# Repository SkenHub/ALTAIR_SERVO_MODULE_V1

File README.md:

# ALTAIR_SERVO_MODULE_V1
ALTAIR_SERVO_MODULE_V1 サーボモータ×５のモジュール　stm32f4446
作者の↓
https://github.com/Altairu/ALTAIR_SERVO_MODULE_V1.git

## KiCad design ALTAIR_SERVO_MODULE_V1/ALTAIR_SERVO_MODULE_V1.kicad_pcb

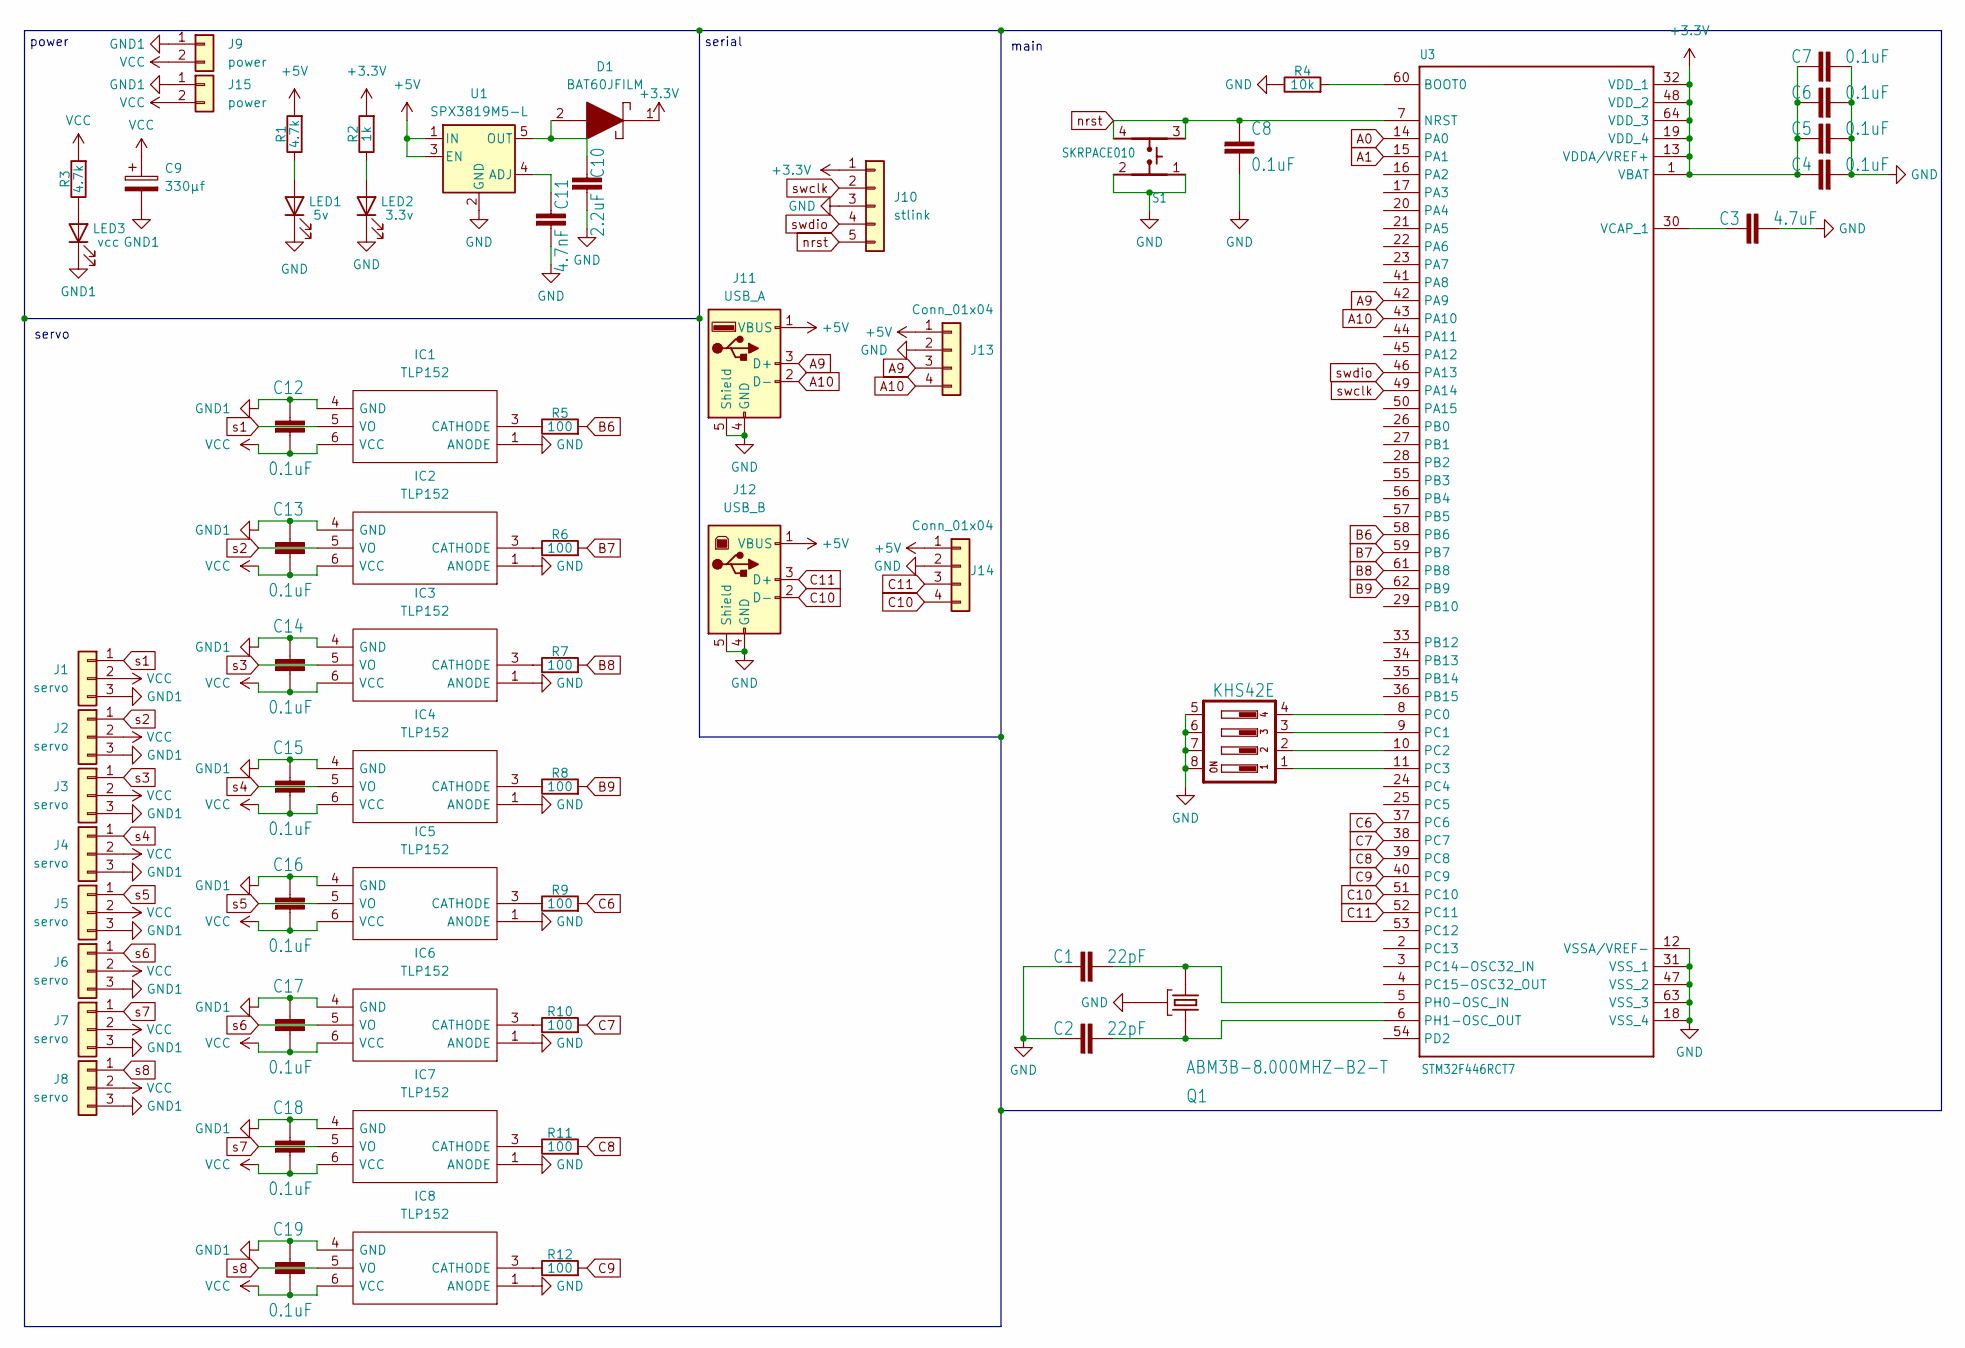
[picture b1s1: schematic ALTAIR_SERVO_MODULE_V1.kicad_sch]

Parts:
C1, C2: 22pF; C_0603_1608Metric
C3: 4.7uF; C_0603_1608Metric
C4, C5, C6, C7, C8, C12, C13, C14, C15, C16, C17, C18, C19: 0.1uF; C_0603_1608Metric
C9: 330μf; CP_Elec_10x10
C10: 2.2uF; C_0603_1608Metric
C11: 4.7nF; C_0603_1608Metric
D1: BAT60JFILM; SOD2513X117N; Manufacturer_Part_Number BAT60JFILM; Mouser Part Number 511-BAT60JFILM
IC1, IC2, IC3, IC4, IC5, IC6, IC7, IC8: TLP152; 11-4L1S_5-PIN-SOIC_; Manufacturer_Part_Number TLP152; Mouser Part Number N/A
J1, J2, J3, J4, J5, J6, J7, J8: servo; JST_XA_S03B-XASK-1_1x03_P2.50mm_Horizontal
J9, J15: power; AMASS_XT60PW-M_1x02_P7.20mm_Horizontal
J10: stlink; JST_XA_S05B-XASK-1_1x05_P2.50mm_Horizontal
J11: USB_A; USB_A_Molex_67643_Horizontal
J12: USB_B; USB_B_Lumberg_2411_02_Horizontal
J13, J14: Conn_01x04; JST_XA_B04B-XASK-1_1x04_P2.50mm_Vertical
LED1: 5v; LED_0603_1608Metric
LED2: 3.3v; LED_0603_1608Metric
LED3: vcc; LED_0603_1608Metric
Q1: ABM3B-8.000MHZ-B2-T; Crystal_SMD_Abracon_ABM3B-4Pin_5.0x3.2mm
R1, R3: 4.7k; R_0603_1608Metric
R2: 1k; R_0603_1608Metric
R4: 10k; R_0603_1608Metric
R5, R6, R7, R8, R9, R10, R11, R12: 100; R_0603_1608Metric
S1: SKRPACE010; SMT_4.2X3.2_
S2: KHS42E; SOIC127P600X175-8N
U1: SPX3819M5-L; SOT-23-5
U3: STM32F446RCT7; QFP50P1200X1200X160-64N

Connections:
+3.3V: C4.1, C5.1, C6.1, C7.1, D1.1, J10.1, R2.2, U3.1 (VBAT), U3.13 (VDDA/VREF+), U3.19 (VDD_4), U3.32 (VDD_1), U3.48 (VDD_2), U3.64 (VDD_3)
+5V: J11.1 (VBUS), J12.1 (VBUS), J13.1, J14.1, R1.2, U1.1 (IN), U1.3 (EN)
A0: U3.14 (PA0)
A1: U3.15 (PA1)
A9: J11.3 (D+), J13.3, U3.42 (PA9)
A10: J11.2 (D-), J13.4, U3.43 (PA10)
B6: R5.2, U3.58 (PB6)
B7: R6.2, U3.59 (PB7)
B8: R7.2, U3.61 (PB8)
B9: R8.2, U3.62 (PB9)
C6: R9.2, U3.37 (PC6)
C7: R10.2, U3.38 (PC7)
C8: R11.2, U3.39 (PC8)
C9: R12.2, U3.40 (PC9)
C10: J12.2 (D-), J14.4, U3.51 (PC10)
C11: J12.3 (D+), J14.3, U3.52 (PC11)
GND: C1.1, C2.1, C3.2, C4.2, C5.2, C6.2, C7.2, C8.2, C10.2, C11.2, IC1.1 (ANODE), IC2.1 (ANODE), IC3.1 (ANODE), IC4.1 (ANODE), IC5.1 (ANODE), IC6.1 (ANODE), IC7.1 (ANODE), IC8.1 (ANODE), J10.3, J11.4 (GND), J11.5 (Shield), J12.4 (GND), J12.5 (Shield), J13.2, J14.2, LED1.1 (K), LED2.1 (K), Q1.2 (GND), Q1.4 (GND), R4.1, S1.1, S1.2, S2.5, S2.6, S2.7, S2.8, U1.2 (GND), U3.12 (VSSA/VREF-), U3.18 (VSS_4), U3.31 (VSS_1), U3.47 (VSS_2), U3.63 (VSS_3)
GND1: C9.2, C12.1, C13.1, C14.1, C15.1, C16.1, C17.1, C18.1, C19.1, IC1.4 (GND), IC2.4 (GND), IC3.4 (GND), IC4.4 (GND), IC5.4 (GND), IC6.4 (GND), IC7.4 (GND), IC8.4 (GND), J1.3, J2.3, J3.3, J4.3, J5.3, J6.3, J7.3, J8.3, J9.1, J15.1, LED3.1 (K)
unnamed: IC1.3 (CATHODE), R5.1
unnamed: IC2.3 (CATHODE), R6.1
unnamed: IC3.3 (CATHODE), R7.1
unnamed: IC4.3 (CATHODE), R8.1
unnamed: IC5.3 (CATHODE), R9.1
unnamed: IC6.3 (CATHODE), R10.1
unnamed: IC7.3 (CATHODE), R11.1
unnamed: IC8.3 (CATHODE), R12.1
unnamed: LED1.2 (A), R1.1
unnamed: LED2.2 (A), R2.1
unnamed: LED3.2 (A), R3.1
unnamed: C11.1, U1.4 (ADJ)
unnamed: C10.1, D1.2, U1.5 (OUT)
unnamed: R4.2, U3.60 (BOOT0)
unnamed: S2.4, U3.8 (PC0)
unnamed: S2.3, U3.9 (PC1)
unnamed: S2.2, U3.10 (PC2)
unnamed: S2.1, U3.11 (PC3)
unnamed: C1.2, Q1.1, U3.5 (PH0-OSC_IN)
unnamed: C2.2, Q1.3, U3.6 (PH1-OSC_OUT)
unnamed: C3.1, U3.30 (VCAP_1)
VCC: C9.1, C12.2, C13.2, C14.2, C15.2, C16.2, C17.2, C18.2, C19.2, IC1.6 (VCC), IC2.6 (VCC), IC3.6 (VCC), IC4.6 (VCC), IC5.6 (VCC), IC6.6 (VCC), IC7.6 (VCC), IC8.6 (VCC), J1.2, J2.2, J3.2, J4.2, J5.2, J6.2, J7.2, J8.2, J9.2, J15.2, R3.2
nrst: C8.1, J10.5, S1.3, S1.4, U3.7 (NRST)
s1: IC1.5 (VO), J1.1
s2: IC2.5 (VO), J2.1
s3: IC3.5 (VO), J3.1
s4: IC4.5 (VO), J4.1
s5: IC5.5 (VO), J5.1
s6: IC6.5 (VO), J6.1
s7: IC7.5 (VO), J7.1
s8: IC8.5 (VO), J8.1
swclk: J10.2, U3.49 (PA14)
swdio: J10.4, U3.46 (PA13)

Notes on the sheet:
serial
main
power
servo

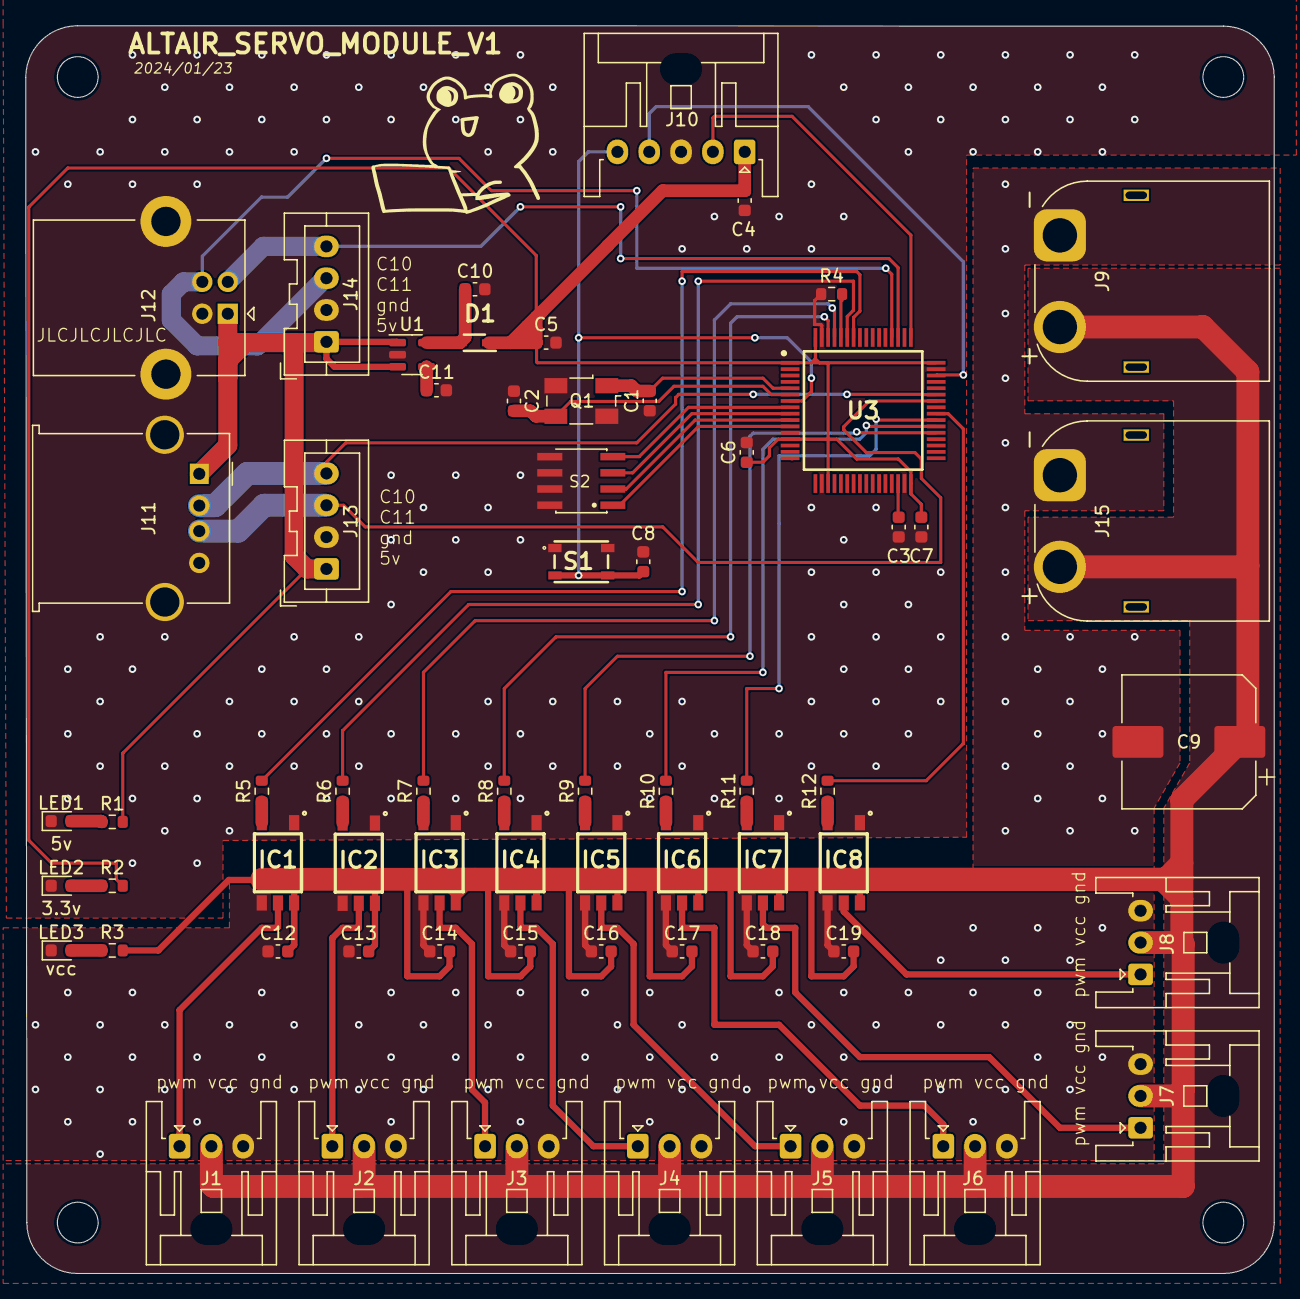
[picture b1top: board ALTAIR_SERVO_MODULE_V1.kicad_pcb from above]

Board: 2 copper layers, 98.1 x 98.0 mm, 63 parts (0 on the bottom side), 49 nets.
